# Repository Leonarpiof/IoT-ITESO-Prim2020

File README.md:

# IoT-ITESO-Prim2020
This repo contains the documentation and generated files during the IoT project of spring 2020 at ITESO, by Leon Arpio Fernandez

## Folders
### Arduino
Contains the source code of the project, in which the sensors are read, and data is sent through cellular network, 
using MQTT. This project is made for the Arduino MKR GSM 1400.

This project uses the following libraries:
- [Arduino MKR GSM libraries](https://github.com/arduino-libraries/MKRGSM)
- [MQTT library for Arduino](https://github.com/256dpi/arduino-mqtt)
- [I2C Soil Moisture Sensor](https://github.com/Apollon77/I2CSoilMoistureSensor)

### Documentation
Contains the documentation made during the project, which contains the research plan, comparative tables, requirements, business model,
customer journey, and others. **All documentas are in Spanish**.

### Lambda
Contains the Lambda deploy package, which has the lambda function handler, and the necessary libraries for the project to work, that are not included in AWS Lambda. Developed in Python 3.8. For the Lambda deploy package download Python library [requests](https://requests.readthedocs.io/en/master/).

To install the library in a specific folder, navigate in the command line to the desired folder, and use the following command.

```
pip install requests -t .
```
- Download [pip](https://pip.pypa.io/en/stable/reference/pip_download/)

### Schematics
Contains the schematic, board file and BOM. Schematic based on [Arduino MKR GSM 1400 schematic](https://store.arduino.cc/usa/mkr-gsm-1400).

### Scripts
Contains Python scripts to test different elements such as Ubidots, Mosquitto, and other features. For this scripts to work, it is necessary to install paho-mqtt and requests. Scripts developed in Python 3.8.1

# Author
León Arpio Fernández

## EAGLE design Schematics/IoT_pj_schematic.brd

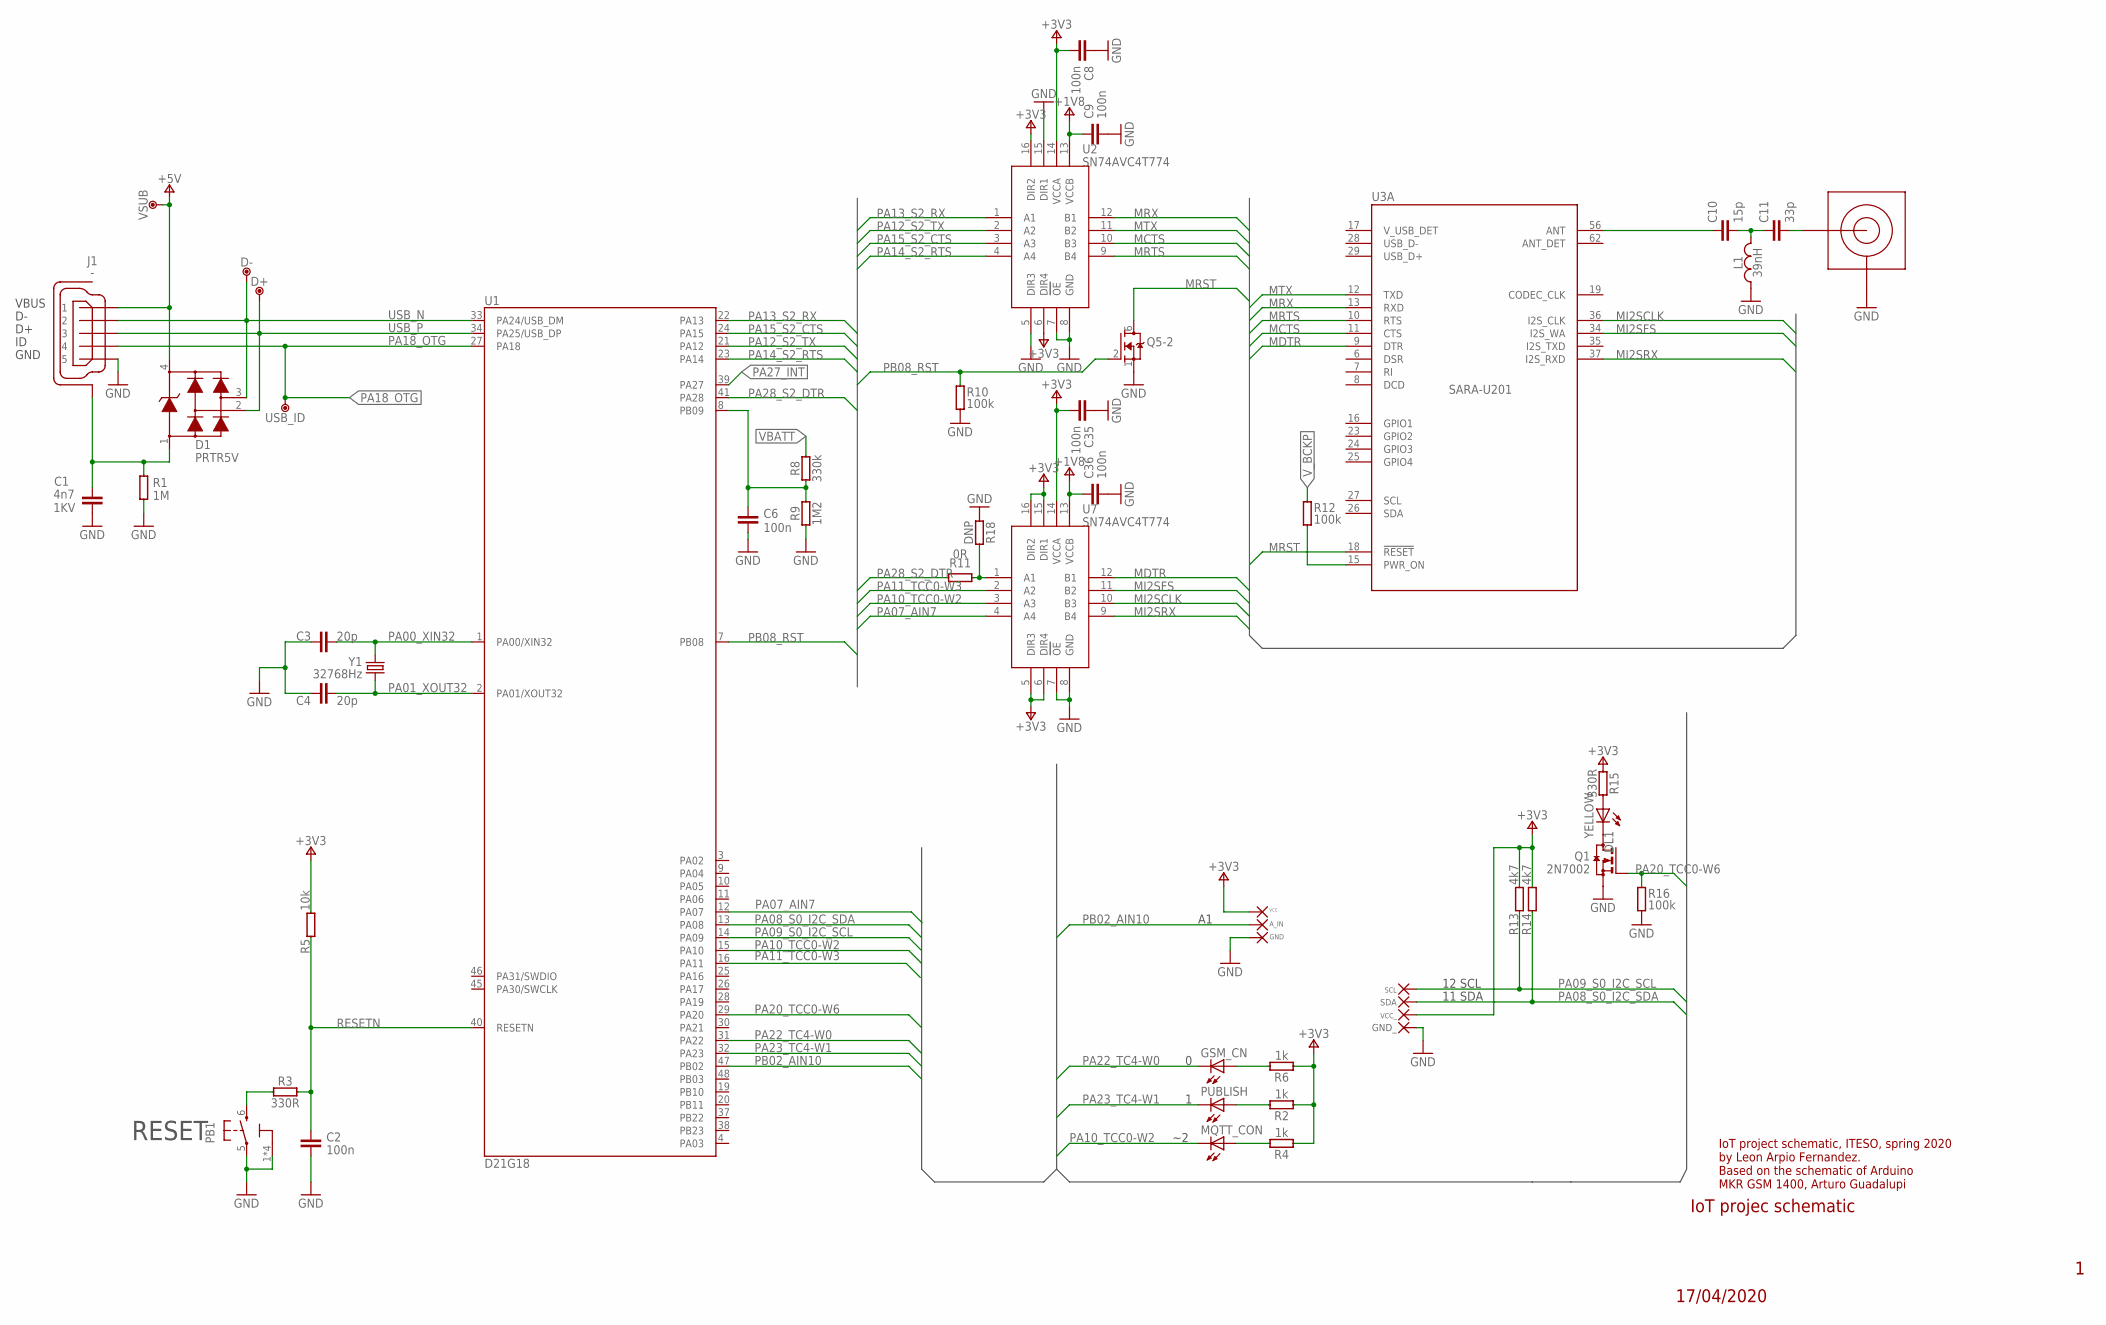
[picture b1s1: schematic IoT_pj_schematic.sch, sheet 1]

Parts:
A_IN: 2,15/1,0
C1: 4n7; 0805-R2013X50N; VOLTAGE 1KV
C2, C6, C8, C9, C35, C36: 100n; 0402-1005X55N
C3, C4: 20p; 0402-1005X55N
C10: 15p; 0402-1005X55N
C11: 33p; 0402-1005X55N
D1: PRTR5V; SOT190P230X110-4N
D+: DNP; TP-1.00MM
D-: DNP; TP-1.00MM
DL1: YELLOW; LEDC1608X80N-AK
GND: 2,15/1,0
GND_: 2,15/1,0
GSM_CN: LEDSML0603; SML0603
J1: -; ZX62-AB-5PA
J6: -; U.FL-R-SMT-1(60)
L1: 39nH; C0402
MQTT_CON: LEDSML0603; SML0603
PB1: PTS820; C&K_PTS820_NO_HOLES
PUBLISH: LEDSML0603; SML0603
Q1: 2N7002; SOTFL50P160X78-3
Q5: 2N7002DW-7-FNO_PAD; PWR_SC70-6L2
R1: 1M; 0402-1005X55N
R2, R4, R6: 1k; 0402-1005X55N
R3, R15: 330R; 0402-1005X55N
R5: 10k; 0402-1005X55N
R8: 330k; 0402-1005X55N
R9: 1M2; 0402-1005X55N
R10, R12, R16: 100k; 0402-1005X55N
R11: 0R; 0402-1005X55N
R13, R14: 4k7; 0402-1005X55N
R18: DNP; 0402-1005X55N
SCL: 2,15/1,0
SDA: 2,15/1,0
U1: D21G18; QFN50P700X700X90-49XN-EPSQ515
U2, U7: SN74AVC4T774; RSV
U3: SARA-U201; SARA-96
USB_ID: DNP; TP-1.00MM
VCC: 2,15/1,0
VCC_: 2,15/1,0
VSUB: DNP; TP-1.00MM
Y1: 32768Hz; ABS07

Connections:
+1V8: C9.1, C36.1, U2.13 (VCCB), U7.13 (VCCB); also elsewhere on the board
+3V3: C8.2, C35.2, R2.1, R4.1, R5.2, R6.1, R13.2, R14.2, R15.1, U2.6 (DIR4), U2.14 (VCCA), U2.16 (DIR2), U7.5 (DIR3), U7.6 (DIR4), U7.14 (VCCA), U7.15 (DIR1), U7.16 (DIR2), VCC.1, VCC_.1; also elsewhere on the board
+5V: D1.4, J1.1, VSUB.X; also elsewhere on the board
GND: C1.2, C2.2, C3.1, C4.1, C6.2, C8.1, C9.2, C35.1, C36.2, GND.1, GND_.1, J1.5, J6.GND1 (GND), J6.GND2 (GND), L1.1, PB1.1 (3), PB1.2 (3), PB1.3, PB1.4 (3), PB1.5 (1), Q1.S, Q5.1 (S), R1.1, R9.1, R10.1, R16.1, R18.1, U2.5 (DIR3), U2.7 (OE), U2.8 (GND), U2.15 (DIR1), U7.7 (OE), U7.8 (GND); also elsewhere on the board
MCTS: U2.10 (B3), U3.11 (CTS)
MDTR: U3.9 (DTR), U7.12 (B1)
MI2SCLK: U3.36 (I2S_CLK), U7.10 (B3)
MI2SFS: U3.34 (I2S_WA), U7.11 (B2)
MI2SRX: U3.37 (I2S_RXD), U7.9 (B4)
MRST: Q5.6 (D), U3.18 (!RESET)
MRTS: U2.9 (B4), U3.10 (RTS)
MRX: U2.12 (B1), U3.13 (RXD)
MTX: U2.11 (B2), U3.12 (TXD)
N17658775: PB1.6 (2), R3.1
unnamed: C1.1, D1.1, J1.6 (SH), J1.7 (SH), J1.8 (SH), J1.9 (SH), J1.10 (SH), J1.11 (SH), R1.2
unnamed: GSM_CN.A, R6.2
unnamed: PUBLISH.A, R2.2
unnamed: C10.1, U3.56 (ANT)
unnamed: C6.1, R8.1, R9.2, U1.8 (PB09)
unnamed: DL1.A, R15.2
unnamed: C11.2, J6.SIG
unnamed: R11.1, R18.2, U7.1 (A1)
unnamed: DL1.C, Q1.D
unnamed: R12.1, U3.15 (PWR_ON)
unnamed: C10.2, C11.1, L1.2
unnamed: MQTT_CON.A, R4.2
PA00_XIN32: C3.2, U1.1 (PA00/XIN32), Y1.2
PA01_XOUT32: C4.2, U1.2 (PA01/XOUT32), Y1.1
PA07_AIN7: U1.12 (PA07), U7.4 (A4)
PA08_S0_I2C_SDA: R14.1, SDA.1, U1.13 (PA08); also elsewhere on the board
PA09_S0_I2C_SCL: R13.1, SCL.1, U1.14 (PA09); also elsewhere on the board
PA10_TCC0-W2: MQTT_CON.C, U1.15 (PA10), U7.3 (A3)
PA11_TCC0-W3: U1.16 (PA11), U7.2 (A2)
PA12_S2_TX: U1.21 (PA12), U2.2 (A2)
PA13_S2_RX: U1.22 (PA13), U2.1 (A1)
PA14_S2_RTS: U1.23 (PA14), U2.4 (A4)
PA15_S2_CTS: U1.24 (PA15), U2.3 (A3)
PA18_OTG: J1.4, U1.27 (PA18), USB_ID.X; also elsewhere on the board
PA20_TCC0-W6: Q1.G, R16.2, U1.29 (PA20)
PA22_TC4-W0: GSM_CN.C, U1.31 (PA22)
PA23_TC4-W1: PUBLISH.C, U1.32 (PA23)
PA27_INT: U1.39 (PA27); also elsewhere on the board
PA28_S2_DTR: R11.2, U1.41 (PA28)
PB02_AIN10: A_IN.1, U1.47 (PB02)
PB08_RST: Q5.2 (G), R10.2, U1.7 (PB08)
RESETN: C2.1, R3.2, R5.1, U1.40 (RESETN)
USB_N: D1.3, D-.X, J1.2, U1.33 (PA24/USB_DM); also elsewhere on the board
USB_P: D1.2, D+.X, J1.3, U1.34 (PA25/USB_DP); also elsewhere on the board
VBATT: R8.2; also elsewhere on the board
V_BCKP: R12.2; also elsewhere on the board

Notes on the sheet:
12 SCL
11 SDA
RESET
IoT project schematic, ITESO, spring 2020 by Leon Arpio Fernandez. Based on the schematic of Arduino MKR GSM 1400, Arturo Guadalupi
IoT projec schematic
17/04/2020

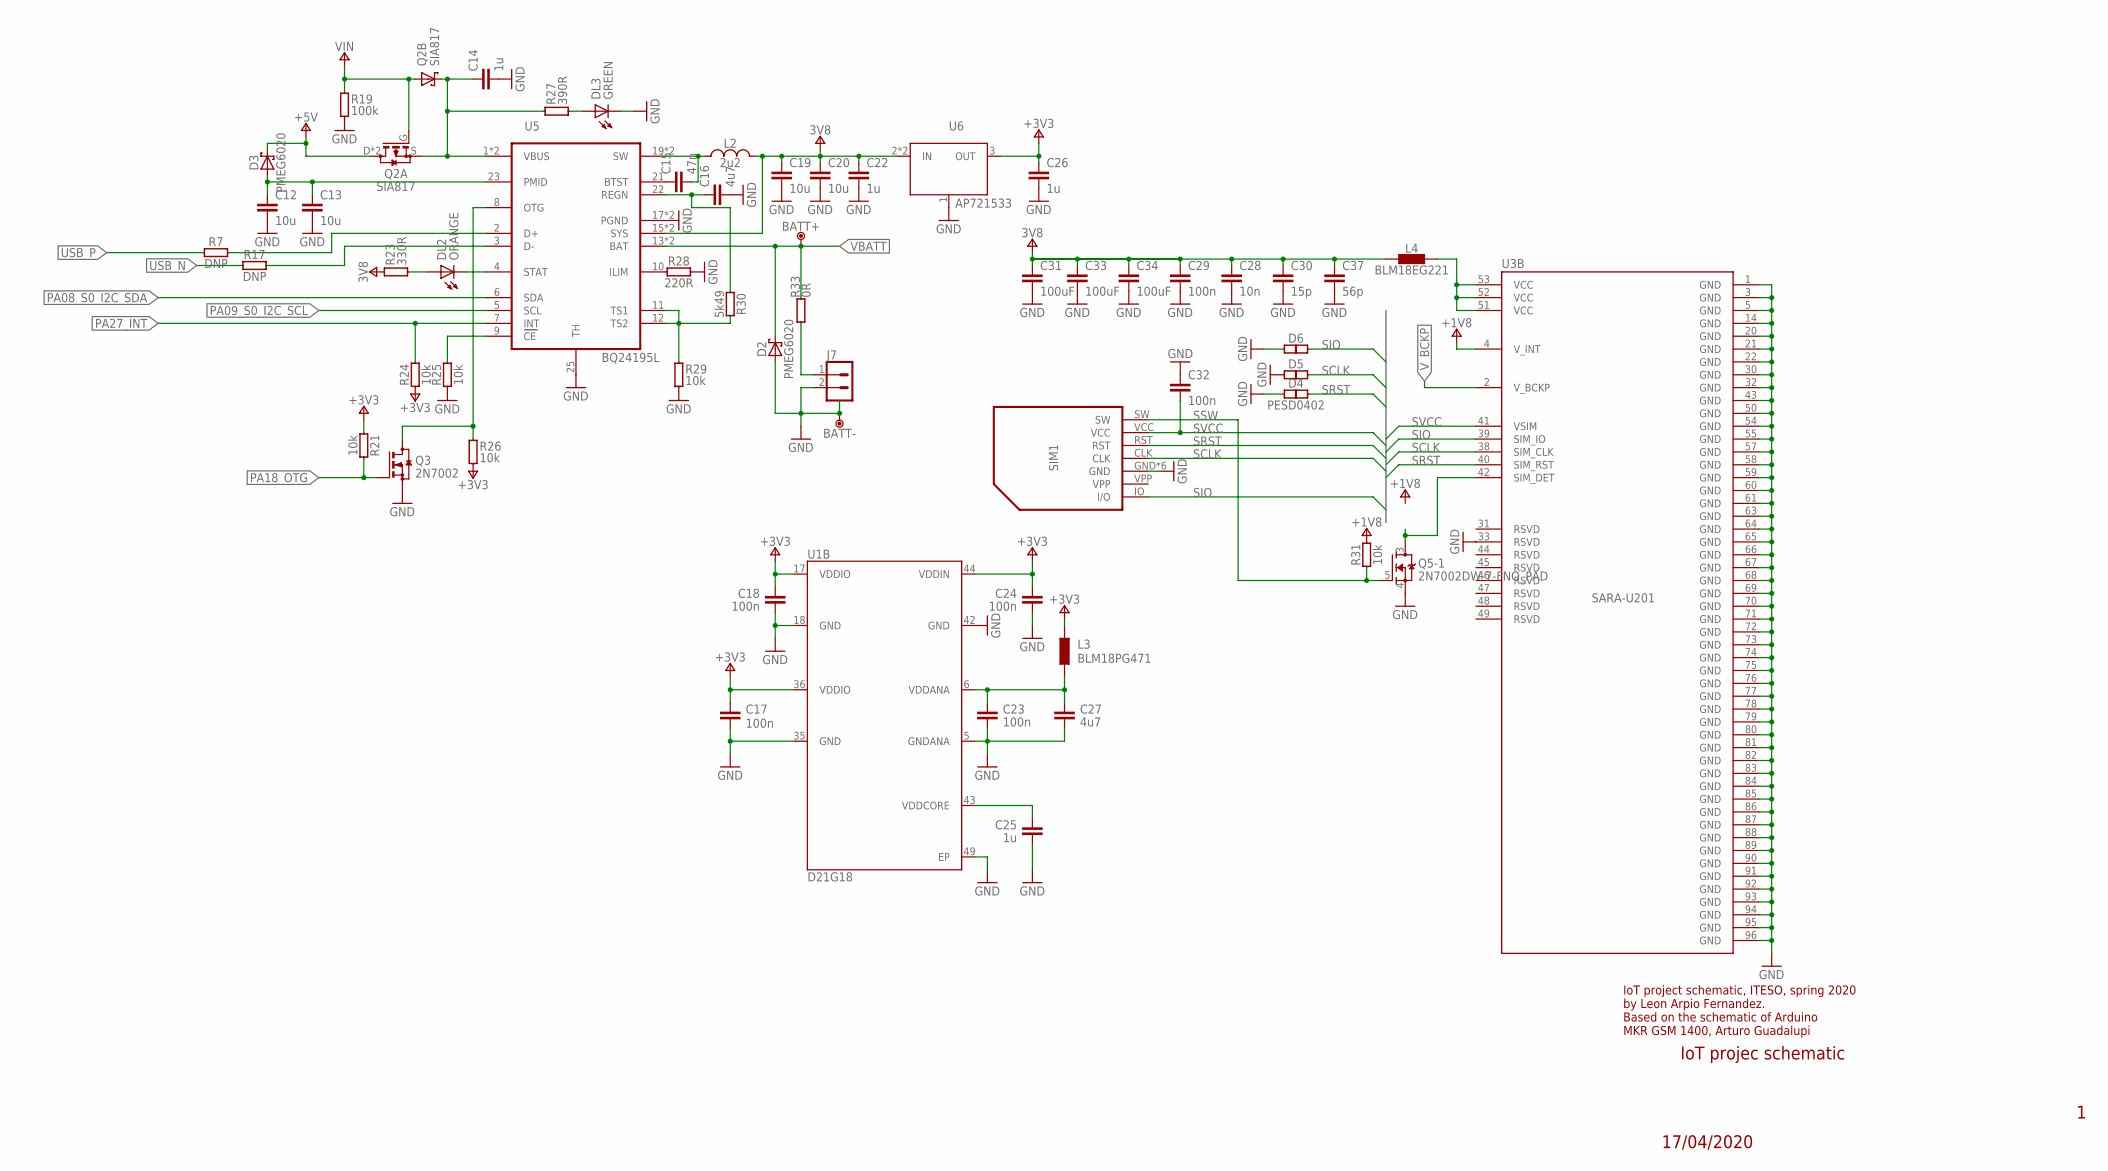
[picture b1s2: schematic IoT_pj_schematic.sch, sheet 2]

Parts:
BATT+: DNP; TP-1.00MM
BATT-: DNP; TP-1.00MM
C12, C13, C19, C20: 10u; 0603-1608X90N
C14, C22, C25, C26: 1u; 0402-1005X55N
C15: 47n; 0402-1005X55N
C16: 4u7; 0402-1005X55N
C17, C18, C23, C24, C29, C32: 100n; 0402-1005X55N
C27: 4u7; 0603-1608X90N
C28: 10n; 0402-1005X55N
C30: 15p; 0402-1005X55N
C31, C33, C34: 100uF; C1206
C37: 56p; 0402-1005X55N
D2, D3: PMEG6020; SODFL3517X110N
D4, D5, D6: PESD0402; 0402-1005X55N
DL2: ORANGE; LEDC1608X80N-AK
DL3: GREEN; LEDC1608X80N-AK
J7: -; JST-S2B-PH-SM4-TB
L2: 2u2; SRP4020
L3: BLM18PG471; 0603-1608X90N
L4: BLM18EG221; 0603-1608X90N
Q2: SIA817; SON65P205X205X75-8N-MWSD
Q3: 2N7002; SOTFL50P160X78-3
Q5: 2N7002DW-7-FNO_PAD; PWR_SC70-6L2
R7, R17: DNP; 0402-1005X55N
R19: 100k; 0402-1005X55N
R21, R24, R25, R26, R29, R31: 10k; 0402-1005X55N
R23: 330R; 0402-1005X55N
R27: 390R; 0402-1005X55N
R28: 220R; 0402-1005X55N
R30: 5k49; 0402-1005X55N
R33: 0R; C0603
SIM1: -; MICROSIM8
U1: D21G18; QFN50P700X700X90-49XN-EPSQ515
U3: SARA-U201; SARA-96
U5: BQ24195L; QFN24
U6: AP721533; SOT89-3L

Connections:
+1V8: R31.2, U3.4 (V_INT); also elsewhere on the board
+3V3: C17.1, C18.1, C24.1, C26.1, L3.1, R21.1, R24.1, R26.1, U1.17 (VDDIO), U1.36 (VDDIO), U1.44 (VDDIN), U6.3 (OUT); also elsewhere on the board
+3V8: C19.1, C20.1, C22.1, C28.1, C29.1, C30.1, C31.1, C33.1, C34.1, C37.1, L2.2, L4.1, R23.2, U5.15 (SYS), U5.16 (SYS), U6.2 (IN), U6.TH (IN)
+5V: D3.C, Q2.D, Q2.D2 (D); also elsewhere on the board
GND: BATT-.X, C12.2, C13.2, C14.2, C16.2, C17.2, C18.2, C19.2, C20.2, C22.2, C23.2, C24.2, C25.2, C26.2, C27.2, C28.2, C29.2, C30.2, C31.2, C32.1, C33.2, C34.2, C37.2, D2.A, D4.1, D5.1, D6.1, DL3.C, J7.2, J7.3 (SH), J7.4 (SH), Q3.S, Q5.4 (S), R19.1, R25.1, R28.2, R29.1, SIM1.GND, SIM1.SH1 (GND), SIM1.SH2 (GND), SIM1.SH3 (GND), SIM1.SH4 (GND), SIM1.SH5 (GND), U1.5 (GNDANA), U1.18 (GND), U1.35 (GND), U1.42 (GND), U1.49 (EP), U3.1 (GND), U3.3 (GND), U3.5 (GND), U3.14 (GND), U3.20 (GND), U3.21 (GND), U3.22 (GND), U3.30 (GND), U3.32 (GND), U3.33 (RSVD), U3.43 (GND), U3.50 (GND), U3.54 (GND), U3.55 (GND), U3.57 (GND), U3.58 (GND), U3.59 (GND), U3.60 (GND), U3.61 (GND), U3.63 (GND), U3.64 (GND), U3.65 (GND), U3.66 (GND), U3.67 (GND), U3.68 (GND), U3.69 (GND), U3.70 (GND), U3.71 (GND), U3.72 (GND), U3.73 (GND), U3.74 (GND), U3.75 (GND), U3.76 (GND), U3.77 (GND), U3.78 (GND), U3.79 (GND), U3.80 (GND), U3.81 (GND), U3.82 (GND), U3.83 (GND), U3.84 (GND), U3.85 (GND), U3.86 (GND), U3.87 (GND), U3.88 (GND), U3.89 (GND), U3.90 (GND), U3.91 (GND), U3.92 (GND), U3.93 (GND), U3.94 (GND), U3.95 (GND), U3.96 (GND), U5.17 (PGND), U5.18 (PGND), U5.25 (TH), U6.1 (GND/ADJ); also elsewhere on the board
N17798864: DL2.A, R23.1
N17834267: DL3.A, R27.1
N17852357: C23.1, C27.1, L3.2, U1.6 (VDDANA)
N17852431: C25.1, U1.43 (VDDCORE)
unnamed: J7.1, R33.1
unnamed: Q5.3 (D), U3.42 (SIM_DET)
unnamed: L4.2, U3.51 (VCC), U3.52 (VCC), U3.53 (VCC)
unnamed: C15.2, L2.1, U5.19 (SW), U5.20 (SW)
unnamed: R7.2, U5.2 (D+)
unnamed: C14.1, Q2.K (C), Q2.K2 (C), Q2.S, R27.2, U5.1 (VBUS), U5.24 (VBUS)
unnamed: C15.1, U5.21 (BTST)
unnamed: R28.1, U5.10 (ILIM)
unnamed: R17.2, U5.3 (D-)
unnamed: C16.1, R30.1, U5.22 (REGN)
unnamed: Q3.D, R26.2, U5.8 (OTG)
unnamed: R29.2, R30.2, U5.11 (TS1), U5.12 (TS2)
unnamed: R25.2, U5.9 (CE)
PA08_S0_I2C_SDA: U5.6 (SDA); also elsewhere on the board
PA09_S0_I2C_SCL: U5.5 (SCL); also elsewhere on the board
PA18_OTG: Q3.G, R21.2; also elsewhere on the board
PA27_INT: R24.2, U5.7 (INT); also elsewhere on the board
SCLK: D5.2, SIM1.CLK, U3.38 (SIM_CLK)
SIO: D6.2, SIM1.IO (I/O), U3.39 (SIM_IO)
SRST: D4.2, SIM1.RST, U3.40 (SIM_RST)
SSW: Q5.5 (G), R31.1, SIM1.SW
STAT: DL2.C, U5.4 (STAT)
SVCC: C32.2, SIM1.VCC, U3.41 (VSIM)
USB_N: R17.1; also elsewhere on the board
USB_P: R7.1; also elsewhere on the board
VBATT: BATT+.X, D2.C, R33.2, U5.13 (BAT), U5.14 (BAT); also elsewhere on the board
VIN: Q2.A, Q2.G, R19.2
VUSB1: C12.1, C13.1, D3.A, U5.23 (PMID)
V_BCKP: U3.2 (V_BCKP); also elsewhere on the board

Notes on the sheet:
IoT project schematic, ITESO, spring 2020 by Leon Arpio Fernandez. Based on the schematic of Arduino MKR GSM 1400, Arturo Guadalupi
IoT projec schematic
17/04/2020

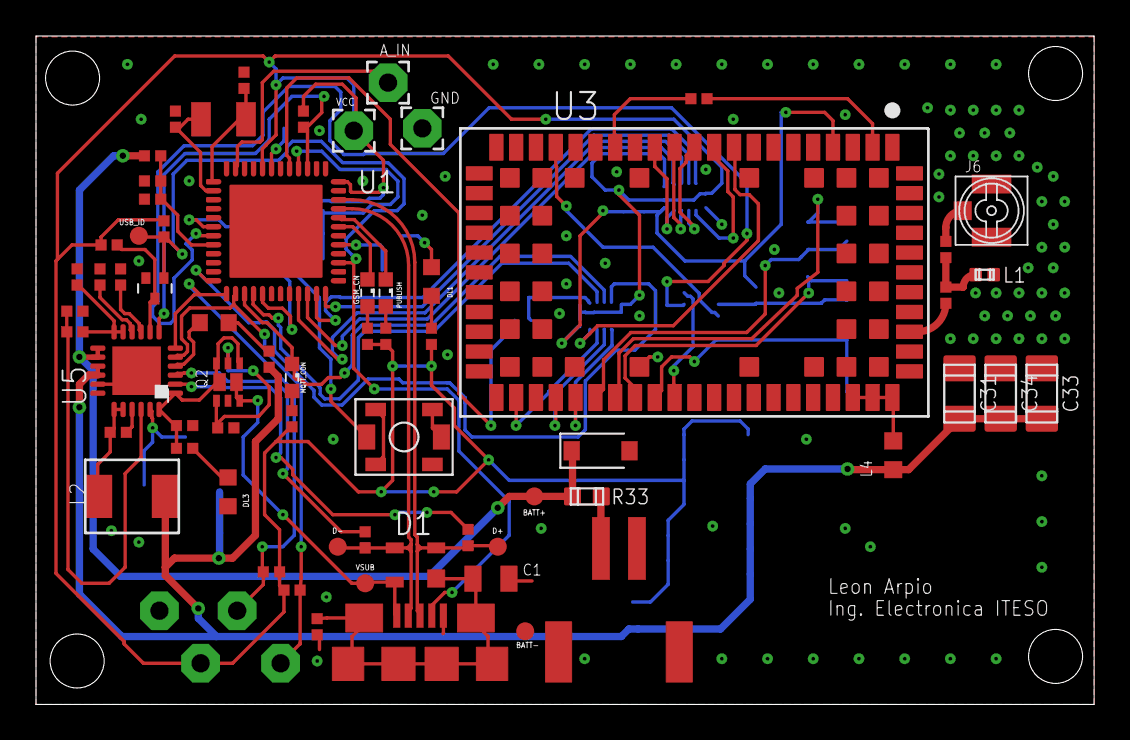
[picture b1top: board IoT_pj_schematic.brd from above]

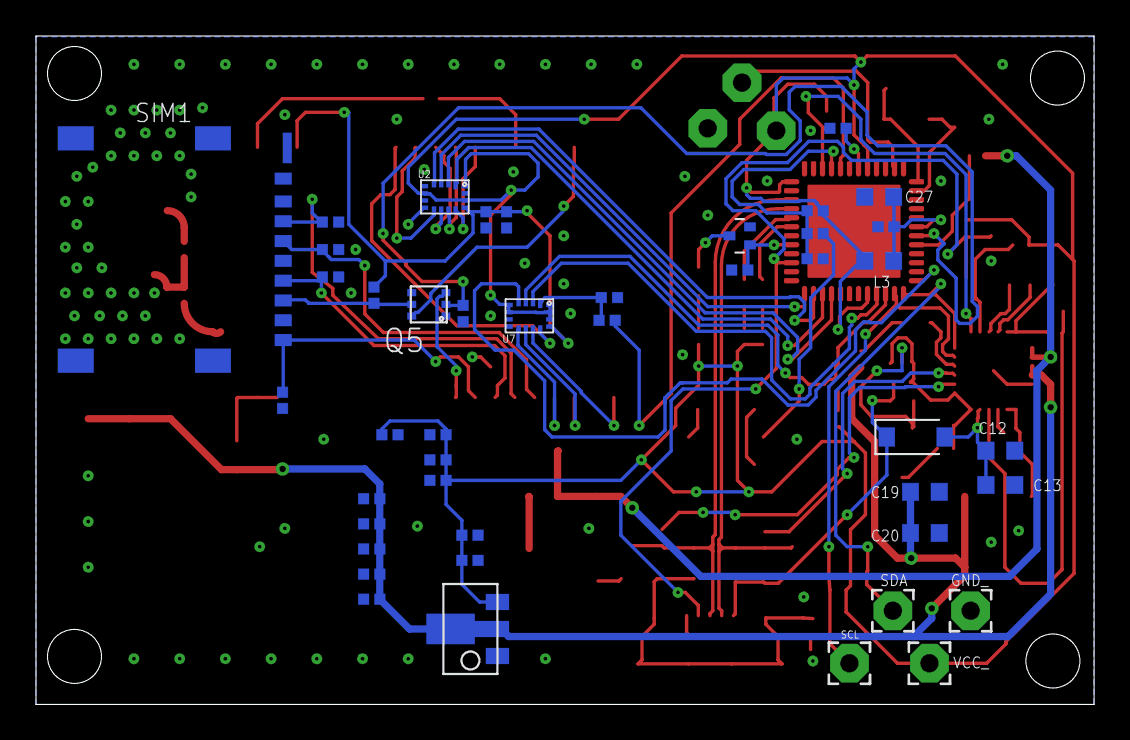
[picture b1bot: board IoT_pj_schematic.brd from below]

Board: 2 copper layers, 58.8 x 37.1 mm, 109 parts (50 on the bottom side), 76 nets.

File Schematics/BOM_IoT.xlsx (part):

| Item | Schematic reference | Qty | Price per unit (USD) | Total price (USD) | Decription | Value | Package | Manufacturer part number | Manufacturer | Distributor | Link | Notas
 | 1 | C1 | 1 | 0.63400000000000001 | 0.63400000000000001 | CAP CER 1000V 4.7nF 10% 0805 | 4.7 nF | 0805 | C0805C472KDRACTU | KEMET | Mouser | https://www.mouser.mx/ProductDetail/KEMET/C0805C472KDRACTU?q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
 | 2 | C2, C6, C8, C9, C17, C18, C23, C24, C29, C32, C3, C36 | 12 | 0.156 | 1.8719999999999999 | CAP CER 50V 100nF 10% 0402 | 100 nF | 0402 | C1005X5R1H104K050BB | TDK | Mouser | https://www.mouser.mx/ProductDetail/TDK/C1005X5R1H104K050BB?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
 | 3 | C3, C4 | 2 | 0.247 | 0.49399999999999999 | CAP CER 50V 20pF 5% 0402 | 20 pF | 0402 | CBR04C200J5GAC | KEMET | Mouser | https://www.mouser.mx/ProductDetail/KEMET/CBR04C200J5GAC?qs=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
 | 4 | C10, C30 | 2 | 0.13 | 0.26 | CAP CER 50V 15pF 5% 0402 | 15 pF | 0402 | GRM1555C1H150JA01D | Murata | Mouser | https://www.mouser.mx/ProductDetail/Murata-Electronics/GRM15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 | Revisar tiempos de entrega. Comprar con anticipación
 | 5 | C11 | 1 | 0.13 | 0.13 | CAP CER 50V 33pF 5% 0402 | 33 pF | 0402 | GRM1555C1H330JA01D | Murata | Mouser | https://www.mouser.mx/ProductDetail/Murata-Electronics/GRM15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 | Revisar tiempos de entrega. Comprar con anticipación
 | 6 | C12, C13, C19, C20 | 4 | 0.56000000000000005 | 2.2400000000000002 | CAP CER 16V 10uF 10% 0603 | 10 uF | 0603 | GRM188R61C106KAALD | Murata | Mouser | https://www.mouser.mx/ProductDetail/Murata-Electronics/GRM18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
 | 7 | C14, C22, C25, C26 | 4 | 0.13 | 0.52 | CAP CER 25V 1uF 10% 0402 | 1 uF | 0402 | GRM155R61E105KA12D | Murata | Mouser | https://www.mouser.mx/ProductDetail/Murata-Electronics/GRM15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
 | 8 | C15 | 1 | 0.13 | 0.13 | CAP CER 25V 47nF 10% 0402 | 47 nF | 0402 | GRM155R71E473KA88D | Murata | Mouser | https://www.mouser.mx/ProductDetail/Murata-Electronics/GRM15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
 | 9 | C16 | 1 | 0.2 | 0.2 | CAP CER 6.3V 4.7uF 20% 0402 | 4.7 uF | 0402 | GRM155R60J475ME47D | Murata | Mouser | https://www.mouser.mx/ProductDetail/Murata-Electronics/GRM15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
 | 10 | C27 | 1 | 0.53 | 0.53 | CAP CER 25V 4.7uF 10% 0603 | 4.7 uF | 0603 | GRM188R61E475KE11D | Murata | Mouser | https://www.mouser.mx/ProductDetail/Murata-Electronics/GRM18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
 | 11 | C28 | 1 | 0.13 | 0.13 | CAP CER 50V 10nF 10% 0402 | 10 nF | 0402 | GRM155R71H103KA88J | Murata | Mouser | https://www.mouser.mx/ProductDetail/Murata-Electronics/GRM15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
 | 12 | C21, C33, C34 | 3 | 0.99 | 2.9699999999999998 | CAP CER 6.3V 100uF 20% 1206 | 100 uF | 1206 | GRM31CD80J107ME39L | Murata | Mouser | https://www.mouser.mx/ProductDetail/Murata-Electronics/GRM31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
 | 13 | C37 | 1 | 0.13 | 0.13 | CAP CER 25V 56pF 5% 0402 | 56 pF | 0402 | GRM1555C1E560JA01D | Murata | Mouser | https://www.mouser.mx/ProductDetail/Murata-Electronics/GRM15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
 | 14 | D1 | 1 | 0.66 | 0.66 | DIO 5.5V ESD PROTECTION SOT143 | PRTR5V | SOT-143 | PRTR5V0U2X,215 | Nexperia | Mouser | https://www.mouser.mx/ProductDetail/Nexperia/PRTR5V0U2X215?q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
 | 15 | D2, D3 | 2 | 0.59 | 1.18 | DIO RECT 60V 2A SOD123 | PMEG6020 | SOD-123 | PMEG6020AELRX | Nexperia | Mouser | https://www.mouser.mx/ProductDetail/Nexperia/PMEG6020AELRX?q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
 | 16 | D4, D5, D6 | 3 | 0.66 | 1.98 | DIO 14V 0402 | PESD0402 | 0402 | PESD0402-140 | Littelfuse | Mouser | https://www.mouser.mx/ProductDetail/Littelfuse/PESD0402-140?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
 | 17 | DL1 | 1 | 0.53 | 0.53 | LED YELLOW 2.1V 20mA 0603 | Yellow | 0603 | HSMY-C190 | Broadcom | Mouser | https://www.mouser.mx/ProductDetail/Broadcom-Avago/HSMY-C190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
 | 18 | DL2 | 1 | 0.53 | 0.53 | LED ORANGE 2.1V 20mA 0603 | Orange | 0603 | HSMD-C190 | Broadcom | Mouser | https://www.mouser.mx/ProductDetail/Broadcom-Avago/HSMD-C190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
 | 19 | DL3, PUBLISH | 2 | 0.53 | 1.06 | LED GREEN 2.1V 20mA 0603 | Green | 0603 | HSMG-C190 | Broadcom | Mouser | https://www.mouser.mx/ProductDetail/Broadcom-Avago/HSMG-C190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
 | 20 | GSM_CN | 1 | 0.82 | 0.82 | LED AMBER 1.9V 20mA 0603 | Amber | 0603 | HSMA-C191-T0000 | Broadcom | Mouser | https://www.mouser.mx/ProductDetail/Broadcom-Avago/HSMA-C191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
 | 21 | J1 | 1 | 1.04 | 1.04 | USB MICRO AB RECP | NA | SMT | ZX62-AB-5PA | Hirose | Mouser | https://www.mouser.mx/ProductDetail/Hirose-Connector/ZX62-AB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
 | 22 | J6 | 1 | 1.43 | 1.43 | RF MALE SMT UFL | NA | SMT | U.FL-R-SMT-1(60) | Hirose | Mouser | https://www.mouser.mx/ProductDetail/Hirose-Connector/UFL-R-S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
 | 23 | J7 | 1 | 0.57999999999999996 | 0.57999999999999996 | BATT MALE CONN 2 POS | NA | SMT | S2B-PH-SM4-TB | JST | Digi-Key | https://www.digikey.com.mx/product-detail/es/jst-sales-ameri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
 | 24 | L1 | 1 | 0.13 | 0.13 | IND 200 mA 39nH 0402 | 39 nH | 0402 | LQG15HN39NJ02D | Murata | Mouser | https://www.mouser.mx/ProductDetail/Murata-Electronics/LQG15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
 | 25 | L2 | 1 | 0.7 | 0.7 | IND 6A 2.2uH 4020 | 2.2 uH | 4020 | SRP4020TA-2R2M | Bourns | Mouser | https://www.mouser.mx/ProductDetail/Bourns/SRP4020TA-2R2M?qs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
 | 26 | L3, L4 | 2 | 0.13 | 0.26 | FERR 1A 470Ohm 0603 | 470 Ohm | 0603 | BLM18PG471SN1D | Murata | Mouser | https://www.mouser.mx/ProductDetail/Murata-Electronics/BLM18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
 | 27 | MQTT_CON | 1 | 1 | 1 | LED RED 3.4V 20mA 0603 | Red | 0603 | HSMG-C190 | Broadcom | Mouser | https://www.mouser.mx/ProductDetail/Broadcom-Avago/HSMR-C190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
 | 28 | PB1 | 1 | 0.6 | 0.6 | PUSH BUTTON | NA | SMT | PTS820J25KSMTRLFS | C&K | Mouser | https://www.mouser.mx/ProductDetail/CK/PTS820J25KSMTRLFS?qs=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
 | 29 | Q1, Q3 | 2 | 0.52 | 1.04 | MOSFET 60V 150mW SOT523 | NA | SOT523 | 2N7002T-7-F | Diodes Inc. | Mouser | https://www.mouser.mx/ProductDetail/Diodes-Incorporated/2N70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
 | 30 | Q2 | 1 | 0.65 | 0.65 | MOSFET 30V 12V | NA | SMT | SIA817EDJ-T1-GE3CT-ND | Vishay | Mouser | https://www.mouser.mx/ProductDetail/Vishay-Semiconductors/SI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
 | 31 | Q5 | 1 | 0.39 | 0.39 | MOSFET 60V 200mW | NA | SMT | 2N7002DW-7-F | Diodes Inc. | Mouser | https://www.mouser.mx/ProductDetail/Diodes-Incorporated/2N70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
 | 32 | R1 | 1 | 0.1 | 0.1 | RES 1/16W 1MOhm 1% 0402 | 1 Mohm | 0402 | RC0402FR-071ML | Yaego | Digi-Key | https://www.digikey.com.mx/product-detail/es/yageo/RC0402FR-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
 | 33 | R2, R4, R6 | 3 | 0.13 | 0.39 | RES 1/16W 1kOhm 1% 0402 | 1 kOhm | 0402 | RC0402FR-071KL | Yaego | Mouser | https://www.mouser.mx/ProductDetail/Yageo/RC0402FR-071KL?qs=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
 | 34 | R3, R15, R23 | 3 | 0.13 | 0.39 | RES 1/16W 330Ohm 1% 0403 | 330 Ohm | 0402 | RC0402FR-07330RL | Yaego | Mouser | https://www.mouser.mx/ProductDetail/Yageo/RC0402FR-07330RL?q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
 | 35 | R5, R21, R24, R25, R26, R29, R31 | 7 | 0.13 | 0.91 | RES 1/16W 10kOhm 1% 0402 | 10 kOhm | 0402 | RC0402FR-0710KL | Yaego | Mouser | https://www.mouser.mx/ProductDetail/Yageo/RC0402FR-0710KL?qs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
 | 36 | R7, R17, R18 | 3 | 0 | 0 | RES DNP | DNP | 0402 | DNP | DNP | DNP | DNP | DNP = Do not populate
 | 37 | R8 | 1 | 0.13 | 0.13 | RES 1/16W 330kOhm 5% 0402 | 330 kOhm | 0402 | RC0402JR-07330KL | Yaego | Mouser | https://www.mouser.mx/ProductDetail/Yageo/RC0402JR-07330KL?q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
 | 38 | R9 | 1 | 0.13 | 0.13 | RES 1/16W 1.2MOhm 1% 0402 | 1.2 Mohm | 0402 | RC0402FR-071M2L | Yaego | Mouser | https://www.mouser.mx/ProductDetail/Yageo/RC0402FR-071M2L?qs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
 | 39 | R10, R12, R16, R19 | 4 | 0.13 | 0.52 | RES 1/16W 100kOhm 1% 0402 | 100 kOhm | 0402 | RC0402FR-07100KL | Yaego | Mouser | https://www.mouser.mx/ProductDetail/Yageo/RC0402FR-07100KL?q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
 | 40 | R11, R33 | 2 | 0.13 | 0.26 | RES 1/16W 0Ohm 1% 0402 | 0 Ohm | 0402 | RC0402FR-070RL | Yaego | Mouser | https://www.mouser.mx/ProductDetail/Yageo/RC0402FR-070RL?qs=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
 | 41 | R13, R14 | 2 | 0.13 | 0.26 | RES 1/16W 4.7kOhm 1% 0402 | 4.7 kOhm | 0402 | RC0402FR-074K7L | Yaego | Mouser | https://www.mouser.mx/ProductDetail/Yageo/RC0402FR-074K7L?qs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
 | 42 | R27 | 1 | 0.13 | 0.13 | RES 1/16W 390Ohm 1% 0402 | 390 Ohm | 0402 | RC0402FR-07390RL | Yaego | Mouser | https://www.mouser.mx/ProductDetail/Yageo/RC0402FR-07390RL?q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
 | 43 | R28 | 1 | 0.13 | 0.13 | RES 1/16W 220Ohm 1% 0402 | 220 Ohm | 0402 | CRCW0402220RFKED | Vishay | Mouser | https://www.mouser.mx/ProductDetail/Vishay-Dale/CRCW0402220R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

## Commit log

2020-04-10 Add: Arduino example to publish a message to an MQTT broker
    No SSL/TLS authentication, dummy message sent
2020-04-10 Test change made in README
2020-04-10 Add: Encryption buy XOR
2020-04-11 Add: MQTT over SSL (RSA 2048)
    Commit NOT WORKING
2020-04-11 Fix: Certificates for AWS
2020-04-11 Fix: Use MQTT SSL with library PubSubClient
    Commit not working
2020-04-11 Backup commit
2020-04-12 Initial Lambda commit
2020-04-12 Add: First Lambda test
2020-04-13 Add: Paho-MQTT library to the deploy package
2020-04-13 Add: Gitignore file
2020-04-13 Fix: Lambda function syntax
2020-04-13 Fix: Missing connect callback assignation and loop start
2020-04-13 Add: Sensors readings
2020-04-13 Fix: Lambda message to Ubidots now by HTTP
    MQTT in lambda does not work properly as it only publishes once in a while
2020-04-13 Fix: Delete lambda test execution.
2020-04-13 Fix: Remove prints
2020-04-13 Comment: Commented code
2020-04-13 Add: Function to retreive from XOR encryption
2020-04-13 Fix: Change XOR method to only encrypt values
2020-04-13 FIx: Syntax error
2020-04-14 Add: Message build
    Add: Gets the time from the network
2020-04-14 Fix: Error when building the message
    Commas, quotes and bracers need to be arrays, not single variables as in C
2020-04-14 Data is published correctly in Ubidots
2020-04-14 Lambda according to Arduino message
2020-04-14 Add: Lambda publishes decrypted data to DynamoDB
2020-04-14 Add: Script to listen from Mosquitto and publish to AWS
2020-04-14 Add: Example of HTTP POST
    Instal requests library
2020-04-14 Add: Listener example
    Listener to Mosquitto server
2020-04-14 Add: Ubidots MQTT publish example
2020-04-14 Renamed files
2020-04-14 Add: LEDs logic to show the device's status
    Fix: Luminosity model was incomplete
2020-04-14 Create LICENSE
2020-04-17 Add: Schematic
2020-04-17 Add: Board (Placed, unrouted)
2020-04-18 Add: Board fully routed
    2-layer board
2020-04-18 FIx: Silkscreen names and values corrected
    Corrected the position so they wouldn't overlap
2020-04-18 Add: Credits
    whoops
2020-04-18 Fix: LED 3 name to MQTT_Conn
    Add: Shielding vias
2020-04-18 Add: BOM
2020-04-19 Add: Total BOM price sum
2020-04-19 Add: Price in BOM per 10 prototypes
2020-04-20 Fix: Incorrect formula for luminosity
2020-04-20 Add: No magic numbers, code commented
2020-04-20 Fix: Correction in Lambda code
2020-04-20 Fix: Correction from mistake made in previous commit
    Ups
2020-04-20 Add: Final report
    Missing: Link to video
2020-04-20 Add: Tutorial for AWS
2020-04-20 Fix: Documentation errors

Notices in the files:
parts and their libraries:
Arduino-connectors: Copyright (c) 2016-2017 Arduino LLC.  All right reserved.
